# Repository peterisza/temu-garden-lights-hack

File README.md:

# Temu garden lights hack

I bought 12V-24V outdoor garden lights from Temu. Originally, they had two wires and a remote controller. I modified them to use an addressable three-wire bus (0V, data, 24V) to control them from my smart home. <a href="https://www.youtube.com/shorts/Vp0UermeDtU">Here</a>'s a short youtube video that shows the process and the result. 

Disclaimer: All electrical modifications are performed at your own risk.

### Reverse engineering the lamp

<table border="0">
  <tr>
    <td valign="top">
      
    </td>
    <td valign="top">
      <ul>
        <li><strong>Product Name:</strong> Low Voltage LED Lights</li>
        <li><strong>Model:</strong> CTY-10W</li>
        <li><strong>Serial Number / Seri Numarasi:</strong> RGDC50245</li>
        <li><strong>Manufacturer:</strong> Shenzhen Changtaiying Technology Co., Ltd</li>
        <li><strong>Address:</strong> No. 4 Yintian Road, Bao'an District, Shenzhen City, Guangdong province, China.</li>
      </ul>
    </td>
  </tr>
</table>

Originally, the lamp had an FMD FT60E122 microcontroller in an SO-14 package with the following pinout:

<table border="0">
  <th>
    <tr>
      <td>Pinout</td>
      <td>Board&nbsp;image</td>
    </tr>
  </th>
  <tr>
    <td>
      <table>
        <thead>
          <tr><th>#</th><th>Function</th></tr>
        </thead>
        <tbody>
          <tr><td>1</td><td>VDD (5V)</td></tr>
          <tr><td>2</td><td>Crystal1 (16 MHz)</td></tr>
          <tr><td>3</td><td>Crystal2</td></tr>
          <tr><td>4</td><td>radio recv</td></tr>
          <tr><td>5</td><td>Red PWM 62.8μs (10μs max)</td></tr>
          <tr><td>6</td><td>White PWM 62.8μs (49.2μs max)</td></tr>
          <tr><td>7</td><td>not connected</td></tr>
          <tr><td>8</td><td>Green PWM 62.8μs (49.2μs max)</td></tr>
          <tr><td>9</td><td>not connected</td></tr>
          <tr><td>10</td><td>not connected</td></tr>
          <tr><td>11</td><td>Blue PWM 62.8μs (49.2μs max)</td></tr>
          <tr><td>12</td><td>test point 2</td></tr>
          <tr><td>13</td><td>test point 1</td></tr>
          <tr><td>14</td><td>GND</td></tr>
        </tbody>
      </table>
    </td>
    <td valign="top">
      
    </td>
  </tr>
</table>

### Conversion

Luckily, this mcu is pin-compatible with the Attiny441. These are the steps I did:

### Custom bus physical description
The custom bus uses three wires: 0V, data, 24V. Logical 0: < 1.5V. Logical 1: 3V-24V. Data format: 10000 baud 8N1. The data line is connected to 24V through a 20mA current limiter in the controller. Max cable length: 200m, number of nodes: 31. To send, each node can pull the data line to zero. Currently, the lamps can only receive but not send. For this reason, their address must be hardcoded during programming like so:
<code>make program LAMP_ADDRESS=0</code>.

I used a 3x0.75mm² ÖLFLEX® CLASSIC 400 P cable. It has the same diameter as the original two-wire cable, but is actually certified for outdoor use unlike the original.

### Data Frame Formats
| Size [byte] | Format A | Size [byte] | Format B |
| :---: | :--- | :---: | :--- |
| 1 | 0 < length <= 30 | 1 | length + 32 |
| max 60 | 4x4 bit RGBW | max 30 | 2x4 bit RGBW |
| 2 | fade time in ms | 2 | fade time in ms |
| 1 | brightness | 1 | brightness |
| 1 | CRC | 1 | CRC |

There must be a 2ms pause between frames.

### Colors

The firmware uses a 16kHz PWM with sigma-delta dithering. It can do gamma-correct interpolation, so the perceived brightness is linear between transitions (premium fade effect 🤩).

### The controller
The controller is a DIN rail mounted USB HID device with a cheap STM32C071 mcu. It can handle two bus lines with 30 lamps each. Build/use it at your own risk only.

My smart home server is already a Raspberry Pi which has USB, so I can just connect it. If you want standalone operation or wireless, you should build an ESP32-based controller instead of this STM32-based one.

## Licensing

- **Software:** Licensed under the [MIT License](https://opensource.org/license/mit)
- **Hardware & Documentation:** Licensed under [CERN-OHL-P](https://ohwr.org/project/cernohl/wikis/Documents/CERN-OHL-version-2) / [CC-BY-4.0](https://creativecommons.org/licenses/by/4.0/)

Basically: feel free to use, modify, and share this project, but keep the attribution and don't sue me if something breaks.

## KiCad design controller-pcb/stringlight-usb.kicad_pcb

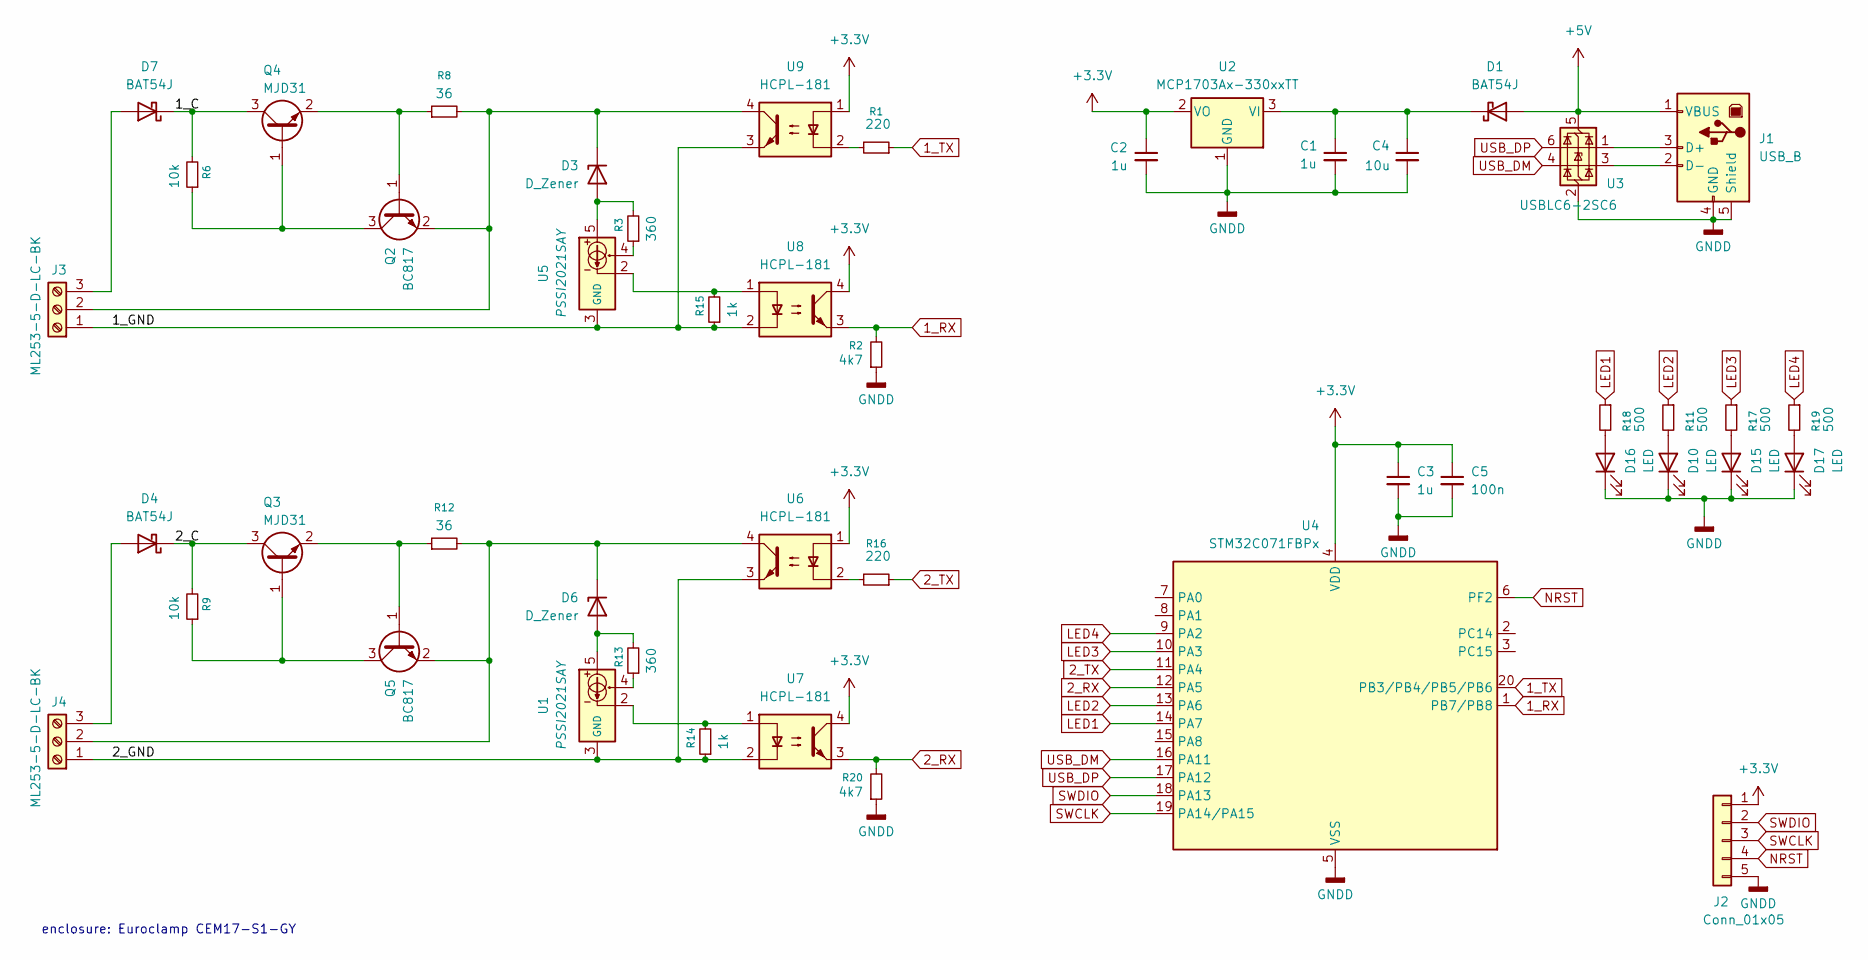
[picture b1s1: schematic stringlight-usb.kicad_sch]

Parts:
C1, C2, C3: 1u; C_0603_1608Metric_Pad1.08x0.95mm_HandSolder
C4: 10u; C_0805_2012Metric_Pad1.18x1.45mm_HandSolder
C5: 100n; C_0603_1608Metric_Pad1.08x0.95mm_HandSolder
D1, D4, D7: BAT54J; D_SOD-323_HandSoldering
D3, D6: D_Zener; D_SOD-123F
D10, D15, D16, D17: LED; LED_Kingbright_APA1606_1.6x0.6mm_Horizontal
J1: USB_B; USB_B_Lumberg_2411_02_Horizontal
J2: Conn_01x05; PinHeader_1x05_P2.54mm_Vertical
J3, J4: ML253-5-D-LC-BK; ML253-5-S-LC
Q2, Q5: BC817; SOT-23
Q3, Q4: MJD31
R1, R16: 220; R_0603_1608Metric_Pad0.98x0.95mm_HandSolder
R2, R20: 4k7; R_0603_1608Metric_Pad0.98x0.95mm_HandSolder
R3, R13: 360; R_0603_1608Metric_Pad0.98x0.95mm_HandSolder
R6, R9: 10k; R_0603_1608Metric_Pad0.98x0.95mm_HandSolder
R8, R12: 36; R_0603_1608Metric_Pad0.98x0.95mm_HandSolder
R11, R17, R18, R19: 500; R_0603_1608Metric_Pad0.98x0.95mm_HandSolder
R14, R15: 1k; R_0603_1608Metric_Pad0.98x0.95mm_HandSolder
U1, U5: PSSI2021SAY; SOT-353_SC-70-5
U2: MCP1703Ax-330xxTT; SOT-23
U3: USBLC6-2SC6; SOT-23-6
U4: STM32C071FBPx; TSSOP-20_4.4x6.5mm_P0.65mm
U6, U7, U8, U9: HCPL-181; SO-4_4.4x3.6mm_P2.54mm

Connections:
1_RX: R2.2, U4.1 (PB7/PB8), U8.3
1_TX: R1.1, U4.20 (PB3/PB4/PB5/PB6)
2_RX: R20.2, U4.12 (PA5), U7.3
2_TX: R16.1, U4.11 (PA4)
+3.3V: C2.1, C3.1, C5.1, J2.1, U2.2 (VO), U4.4 (VDD), U6.1, U7.4, U8.4, U9.1
+5V: D1.2 (A), J1.1 (VBUS), U3.5 (VBUS)
/1_C: D7.1 (K), Q4.3 (C), R6.2
/1_GND: J3.1, R15.1, U5.3 (GND_3), U8.2, U9.3
/2_C: D4.1 (K), Q3.3 (C), R9.2
/2_GND: J4.1, R14.1, U1.3 (GND_3), U6.3, U7.2
GNDD: C1.2, C2.2, C3.2, C4.2, C5.2, D10.1 (K), D15.1 (K), D16.1 (K), D17.1 (K), J1.4 (GND), J1.5 (Shield), J2.5, R2.1, R20.1, U2.1 (GND), U3.2 (GND), U4.5 (VSS)
LED1: R18.1, U4.14 (PA7)
LED2: R11.1, U4.13 (PA6)
LED3: R17.1, U4.10 (PA3)
LED4: R19.1, U4.9 (PA2)
NRST: J2.4, U4.6 (PF2)
unnamed: C1.1, C4.1, D1.1 (K), U2.3 (VI)
unnamed: D3.2 (A), R3.2, U5.5
unnamed: D3.1 (K), J3.2, Q2.2 (E), R8.2, U9.4
unnamed: D4.2 (A), J4.3
unnamed: D6.2 (A), R13.2, U1.5
unnamed: D6.1 (K), J4.2, Q5.2 (E), R12.2, U6.4
unnamed: D7.2 (A), J3.3
unnamed: D10.2 (A), R11.2
unnamed: D15.2 (A), R17.2
unnamed: D16.2 (A), R18.2
unnamed: D17.2 (A), R19.2
unnamed: J1.3 (D+), U3.1 (I/O1)
unnamed: J1.2 (D-), U3.3 (I/O2)
unnamed: Q2.1 (B), Q4.2 (E), R8.1
unnamed: Q2.3 (C), Q4.1 (B), R6.1
unnamed: Q3.1 (B), Q5.3 (C), R9.1
unnamed: Q3.2 (E), Q5.1 (B), R12.1
unnamed: R1.2, U9.2
unnamed: R3.1, U5.4
unnamed: R13.1, U1.4
unnamed: R14.2, U1.2, U7.1
unnamed: R15.2, U5.2, U8.1
unnamed: R16.2, U6.2
SWCLK: J2.3, U4.19 (PA14/PA15)
SWDIO: J2.2, U4.18 (PA13)
USB_DM: U3.4 (I/O2), U4.16 (PA11)
USB_DP: U3.6 (I/O1), U4.17 (PA12)

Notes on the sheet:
enclosure: Euroclamp CEM17-S1-GY

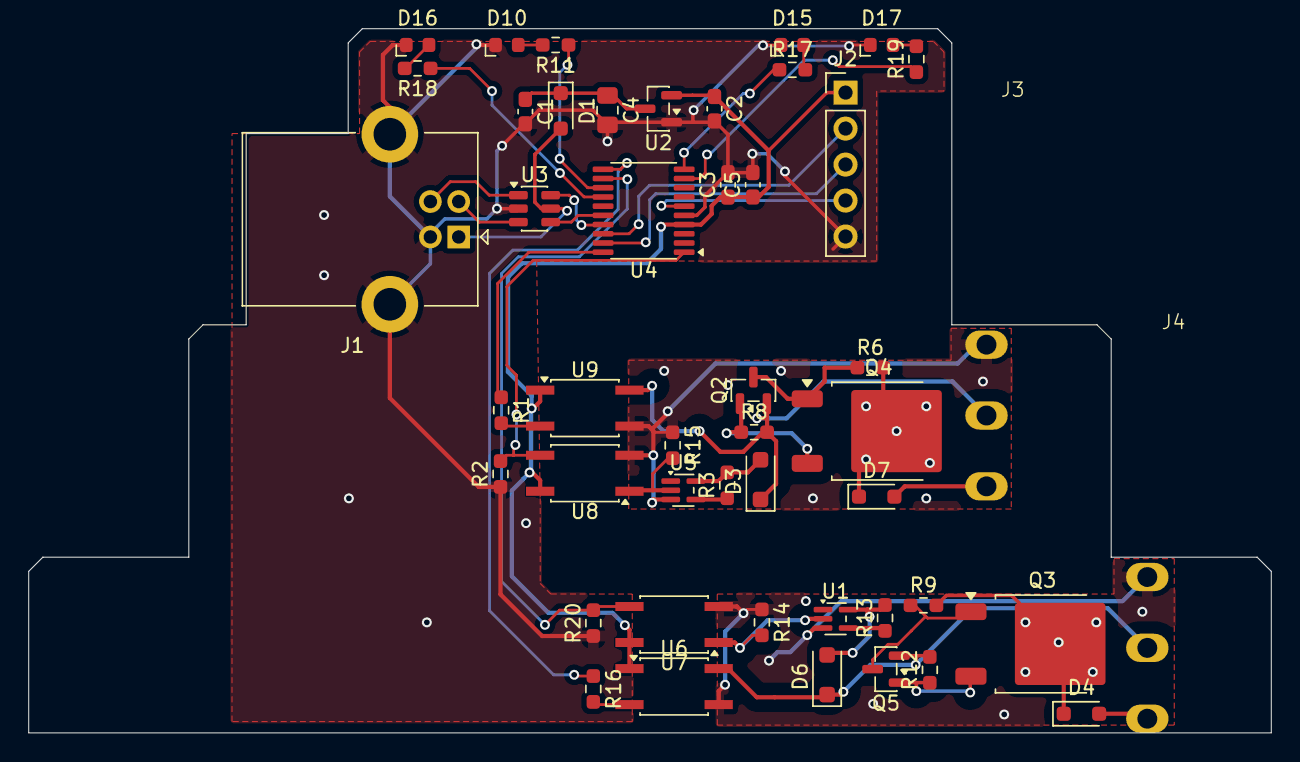
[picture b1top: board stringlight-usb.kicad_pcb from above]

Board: 2 copper layers, 87.7 x 49.7 mm, 47 parts (0 on the bottom side), 43 nets.

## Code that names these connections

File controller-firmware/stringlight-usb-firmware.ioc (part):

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Mcu.Name=STM32C071FBPx
Mcu.Package=TSSOP20_GP
Mcu.UserName=STM32C071FBPx
PA11\ [PA9].Mode=Device
PA11\ [PA9].Signal=USB_DM
PA12\ [PA10].Mode=Device
PA12\ [PA10].Signal=USB_DP
PA14-BOOT0__PA15.StandardMode=true
PA2.Signal=GPIO_Output
PA3.Signal=GPIO_Output
PA4.Mode=Asynchronous
PA4.Signal=USART2_TX
PA5.Mode=Asynchronous
PA5.Signal=USART2_RX
PA6.Signal=GPIO_Output
PA7.Signal=GPIO_Output
PB3__PB4__PB5__PB6.StandardMode=true
PB6.Mode=Asynchronous
PB6.Signal=USART1_TX
PB7.Mode=Asynchronous
PB7.Signal=USART1_RX
PB7__PB8.StandardMode=true
RCC.HSE_VALUE=8000000
RCC.SYSCLKFreq_VALUE=48000000
board=custom

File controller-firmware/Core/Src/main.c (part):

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  /*Configure GPIO pin Output Level */
  HAL_GPIO_WritePin(GPIOA, GPIO_PIN_2|GPIO_PIN_3|GPIO_PIN_6|GPIO_PIN_7, GPIO_PIN_RESET);

  /*Configure GPIO pins : PB8 PB3 PB4 PB5 */
  GPIO_InitStruct.Pin = GPIO_PIN_8|GPIO_PIN_3|GPIO_PIN_4|GPIO_PIN_5;
  GPIO_InitStruct.Mode = GPIO_MODE_ANALOG;
  GPIO_InitStruct.Pull = GPIO_NOPULL;
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  GPIO_InitStruct.Pull = GPIO_NOPULL;
  HAL_GPIO_Init(GPIOC, &GPIO_InitStruct);

  /*Configure GPIO pin : PF2 */
  GPIO_InitStruct.Pin = GPIO_PIN_2;
  GPIO_InitStruct.Mode = GPIO_MODE_ANALOG;
  GPIO_InitStruct.Pull = GPIO_NOPULL;
  HAL_GPIO_Init(GPIOF, &GPIO_InitStruct);

  /*Configure GPIO pins : PA0 PA1 PA8 PA13
                           PA14 PA15 */
  GPIO_InitStruct.Pin = GPIO_PIN_0|GPIO_PIN_1|GPIO_PIN_8|GPIO_PIN_13
                          |GPIO_PIN_14|GPIO_PIN_15;
  GPIO_InitStruct.Mode = GPIO_MODE_ANALOG;
  GPIO_InitStruct.Pull = GPIO_NOPULL;
  HAL_GPIO_Init(GPIOA, &GPIO_InitStruct);

  /*Configure GPIO pins : PA2 PA3 PA6 PA7 */
  GPIO_InitStruct.Pin = GPIO_PIN_2|GPIO_PIN_3|GPIO_PIN_6|GPIO_PIN_7;
  GPIO_InitStruct.Mode = GPIO_MODE_OUTPUT_PP;
  GPIO_InitStruct.Pull = GPIO_NOPULL;
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
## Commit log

2026-05-01 Readme test
2026-05-02 pinout
2026-05-02 label
2026-05-02 steps
2026-05-02 enclosure
2026-05-02 connector
2026-05-02 controller
2026-05-02 phase correct PWM -> fast PWM, increased PWM frequency from 1 kHz to 16 kHz, added dithering
2026-05-03 fixed bug in dithering
2026-05-26 - speed up opto RX with additional 1k resistor - add firmware-based 24V-data short circuit protection (goes into fault mode)

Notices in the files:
controller-firmware/Core/Src/main.c:
Copyright (c) 2026 STMicroelectronics.
All rights reserved.
This software is licensed under terms that can be found in the LICENSE file
